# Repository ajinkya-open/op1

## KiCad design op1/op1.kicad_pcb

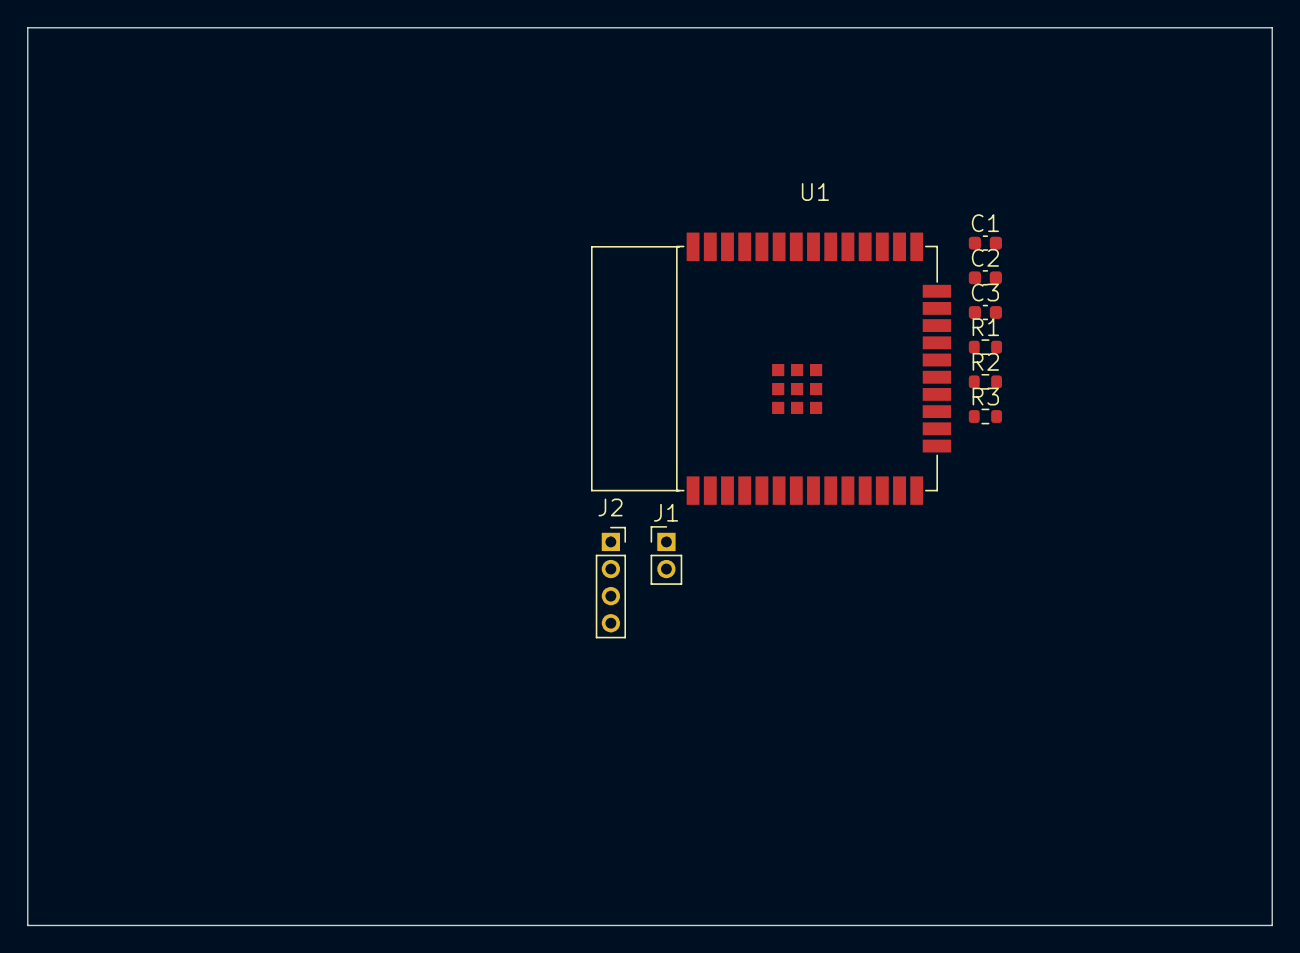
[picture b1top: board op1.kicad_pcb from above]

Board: 2 copper layers, 91.9 x 66.3 mm, 9 parts (0 on the bottom side), 8 nets, no tracks yet.

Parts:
C1, C2, C3: 0.1uF; C_0603_1608Metric
J1: BERG STRIP; PinHeader_1x02_P2.00mm_Vertical
J2: BERG STRIP; PinSocket_1x04_P2.00mm_Vertical
R1, R2, R3: 4K7; R_0603_1608Metric
U1: WIFI-SMD_ESP32-WROOM-32E

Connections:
ESP_RST: C2.1, R1.2, U1.3 (EN)
GND: C1.2, C2.2, C3.2, J1.1, J2.4, U1.1 (GND), U1.38 (GND), U1.39 (GND)
unnamed: J1.2, U1.25 (GPIO0_T1)
RXD0: J2.2, U1.34 (RXD0)
SCL: R2.2, U1.36 (GPIO22_SCL)
SDA: R3.2, U1.33 (GPIO21_SDA)
TXD0: J2.3, U1.35 (TXD0)
VCC_3V: C1.1, C3.1, J2.1, R1.1, R2.1, R3.1, U1.2 (3V3)

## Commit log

2026-03-10 init
2026-03-10 wdewedwd
2026-03-10 eeerr
2026-03-10 wecdsdc
2026-03-10 dvdfvdfv
2026-03-10 sdcsd
2026-03-10 dfvdfv
2026-03-10 removed os
